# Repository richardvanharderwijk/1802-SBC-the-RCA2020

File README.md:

This project is the design of a small microcomputer system based on the RCA 1802 COSMAC CPU. 

The specifications of the system are:

• RCA 1802 CPU; 8 bit; up to 3,2 MHz clockspeed

• 64 kB RAM memory

• 8kBROM

• OS(ish): Utility to save, load, start programs; and examine registers and memory

• TTY serial terminal connection, software UART

• 8 bit parallel in/out

• I2C interface; and a clock/calender unit

• All signals available via connectors

• Single 5V via USB port

The design includes a PCB of 10 x 13 cm; and a build and test protocol per unit to facilitate error finding during build.

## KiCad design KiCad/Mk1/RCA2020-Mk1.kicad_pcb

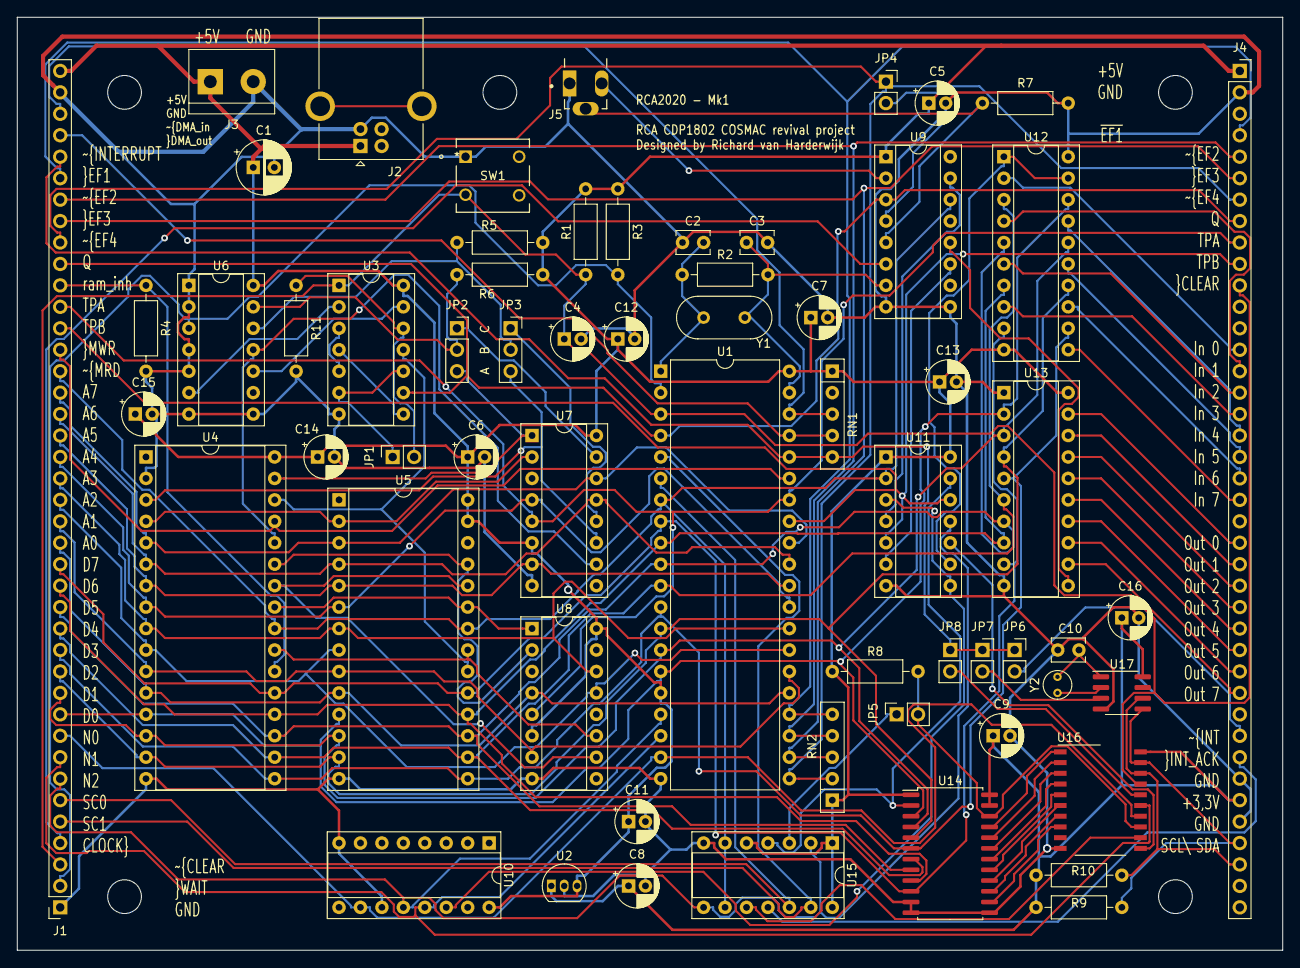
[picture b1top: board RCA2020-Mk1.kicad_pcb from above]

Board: 2 copper layers, 149.9 x 110.5 mm, 62 parts (0 on the bottom side), 106 nets.

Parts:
C1: 10uF; CP_Radial_D6.3mm_P2.50mm
C2, C3: 47pF; C_Disc_D3.8mm_W2.6mm_P2.50mm
C4: 1,5uF; CP_Radial_D5.0mm_P2.00mm
C5, C6, C7, C8, C9, C11, C12, C13, C14, C15, C16: 0,22uF; CP_Radial_D5.0mm_P2.00mm
C10: 20pF; C_Disc_D3.8mm_W2.6mm_P2.50mm
J1, J4: Conn_01x40_Female; PinSocket_1x40_P2.54mm_Vertical
J2: USB_B; USB_B_OST_USB-B1HSxx_Horizontal
J3: Screw_Terminal_01x02; TerminalBlock_bornier-2_P5.08mm
J5: AudioJack3; Lumberg-1501_04-MFG
JP1, JP4, JP5: Jumper_2_Bridged; PinSocket_1x02_P2.54mm_Vertical
JP2, JP3: Jumper_3_Bridged12; PinSocket_1x03_P2.54mm_Vertical
JP6, JP7, JP8: Jumper_2_Open; PinSocket_1x02_P2.54mm_Vertical
R1: 100k; R_Axial_DIN0207_L6.3mm_D2.5mm_P10.16mm_Horizontal
R2: 6,8M; R_Axial_DIN0207_L6.3mm_D2.5mm_P10.16mm_Horizontal
R3, R4, R5, R6, R7, R8, R11: 47k; R_Axial_DIN0207_L6.3mm_D2.5mm_P10.16mm_Horizontal
R9, R10: 4k7; R_Axial_DIN0207_L6.3mm_D2.5mm_P10.16mm_Horizontal
RN1, RN2: 4x47k; R_Array_SIP5
SW1: SW_Push; RAFI_KeySwitch
U1: CDP1802ACE; DIP-40_W15.24mm
U2: L78L33_TO92; TO-92_Inline
U3: 4001; DIP-14_W7.62mm_Socket
U4: 628128_DIP32_SSOP32; DIP-32_W15.24mm_Socket
U5: 28C64; DIP-28_W15.24mm_Socket
U6: 4025; DIP-14_W7.62mm_Socket
U7, U8: 4042; DIP-16_W7.62mm_Socket
U9: 4049; DIP-16_W7.62mm_Socket
U10: 4028; DIP-16_W7.62mm_Socket
U11: 4023; DIP-14_W7.62mm_Socket
U12: 74HCT244; DIP-20_W7.62mm_Socket
U13: 74LS573; DIP-20_W7.62mm_Socket
U14: 74LVC4245AD; SOP-24_7.5x15.4mm_P1.27mm
U15: 4011; DIP-14_W7.62mm_Socket
U16: PCA9564PW; SO-20_12.8x7.5mm_P1.27mm
U17: PCF8563T; SOIC-8_3.9x4.9mm_P1.27mm
Y1: Crystal; Crystal_HC49-U_Vertical
Y2: 32.768 kHz; Crystal_Round_D3.0mm_Vertical

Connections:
+3V3: C8.1, C9.1, C16.1, J4.35, R9.1, R10.1, U2.1, U14.23, U14.24, U16.20, U17.8
+5V: C1.1, C5.1, C6.1, C7.1, C11.1, C12.1, C13.1, C14.1, C15.1, J1.40, J2.1, J3.1, J4.1, R1.1, R3.1, R5.1, R6.1, R8.1, RN1.1, RN2.1, U1.16, U1.40, U2.3, U3.14, U4.32, U5.27, U5.28, U6.14, U7.6, U7.16, U8.6, U8.16, U9.1, U10.16, U11.1, U11.14, U12.10, U13.20, U14.1, U15.1, U15.5, U15.14
/N-lines IO/N-In0: J4.14, U12.2
/N-lines IO/N-In1: J4.15, U12.4
/N-lines IO/N-In2: J4.16, U12.6
/N-lines IO/N-In3: J4.17, U12.8
/N-lines IO/N-In4: J4.18, U12.17
/N-lines IO/N-In5: J4.19, U12.15
/N-lines IO/N-In6: J4.20, U12.13
/N-lines IO/N-In7: J4.21, U12.11
/N-lines IO/N-Out0: J4.23, U13.19
/N-lines IO/N-Out1: J4.24, U13.18
/N-lines IO/N-Out2: J4.25, U13.17
/N-lines IO/N-Out3: J4.26, U13.16
/N-lines IO/N-Out4: J4.27, U13.15
/N-lines IO/N-Out5: J4.28, U13.14
/N-lines IO/N-Out6: J4.29, U13.13
/N-lines IO/N-Out7: J4.30, U13.12
/N-lines to I2C/SCL: J4.38, R10.2, U16.18, U17.6
/N-lines to I2C/SDA: J4.37, R9.2, U16.19, U17.5
/N-lines to I2C/~INT: J4.32, JP6.2
/N-lines to I2C/~INT_ACK: J4.33, U15.11
/RAM+ROM/EXTERNAL_RAM_INHIBIT: J1.30, R4.1, U4.22
A0: J1.18, U1.25, U4.12, U5.10, U8.4
A1: J1.19, U1.26, U4.11, U5.9, U8.7
A2: J1.20, U1.27, U4.10, U5.8, U8.13
A3: J1.21, U1.28, U4.9, U5.7, U8.14
A4: J1.22, U1.29, U4.8, U5.6, U7.4
A5: J1.23, U1.30, U4.7, U5.5, U7.7
A6: J1.24, U1.31, U4.6, U5.4, U7.13
A7: J1.25, U1.32, U4.5, U5.3, U7.14
A8: U4.27, U5.25, U8.2
A9: U4.26, U5.24, U8.10
A10: U4.23, U5.21, U8.11
A11: U4.25, U5.23, U8.1
A12: U4.4, U5.2, U7.2
A13: U4.28, U6.11, U7.10
A14: JP3.3, U4.3, U7.11
A15: JP2.3, U4.31, U7.1
CLOCK: J1.4, U9.6
D0: J1.10, U1.15, U4.13, U5.11, U12.18, U13.2, U14.3
D1: J1.11, U1.14, U4.14, U5.12, U12.16, U13.3, U14.4
D2: J1.12, U1.13, U4.15, U5.13, U12.14, U13.4, U14.5
D3: J1.13, U1.12, U4.17, U5.15, U12.12, U13.5, U14.6
D4: J1.14, U1.11, U4.18, U5.16, U12.3, U13.6, U14.7
D5: J1.15, U1.10, U4.19, U5.17, U12.5, U13.7, U14.8
D6: J1.16, U1.9, U4.20, U5.18, U12.7, U13.8, U14.9
D7: J1.17, U1.8, U4.21, U5.19, U12.9, U13.9, U14.10
GND: C1.2, C2.2, C3.2, C4.2, C5.2, C6.2, C7.2, C8.2, C9.2, C10.2, C11.2, C12.2, C13.2, C14.2, C15.2, C16.2, J1.1, J1.39, J2.4, J3.2, J4.2, J4.34, J4.36, J5.S, R4.2, R7.2, R11.2, SW1.1, U1.20, U2.2, U3.7, U4.2, U4.16, U5.14, U6.1, U6.2, U6.4, U6.5, U6.7, U6.8, U7.8, U8.8, U9.8, U9.9, U10.8, U10.11, U11.7, U12.20, U13.1, U13.10, U14.11, U14.12, U14.13, U15.7, U16.10, U17.4
N0: J1.9, U1.19, U10.10, U16.14
N1: J1.8, U1.18, U10.13, U16.15
N2: J1.7, U1.17, U10.12, U11.11, U15.2, U15.8
unnamed: C2.1, R2.1, U1.1, Y1.1
unnamed: C3.1, R2.2, U1.39, U9.7, Y1.2
unnamed: C10.1, U17.1, Y2.2
unnamed: J5.R, U9.2
unnamed: J5.T, R7.1, U9.5
unnamed: JP1.1, U3.6, U3.10
unnamed: JP1.2, R11.1, U3.12
unnamed: JP2.1, U7.15
unnamed: JP2.2, R6.2, U6.13
unnamed: JP3.1, U7.12
unnamed: JP3.2, R5.2, U6.12
unnamed: JP4.2, U9.4
unnamed: JP5.1, U15.3
unnamed: JP5.2, R8.2, U14.22, U16.13
unnamed: JP7.2, U17.3
unnamed: JP8.2, U16.16
unnamed: U3.2, U6.6
unnamed: U3.3, U3.5
unnamed: U3.4, U3.8
unnamed: U3.11, U4.30, U5.20
unnamed: U3.13, U6.10
unnamed: U10.14, U11.3, U11.8
unnamed: U9.15, U11.4
unnamed: U9.11, U11.6
unnamed: U11.9, U12.1, U12.19
unnamed: U11.10, U16.11
unnamed: U11.13, U14.2, U15.4
unnamed: U9.12, U13.11
unnamed: U14.14, U16.8
unnamed: U14.15, U16.7
unnamed: U14.16, U16.6
unnamed: U14.17, U16.5
unnamed: U14.18, U16.4
unnamed: U14.19, U16.3
unnamed: U14.20, U16.2
unnamed: U14.21, U16.1
unnamed: U15.10, U16.12
unnamed: U17.2, Y2.1
Q: J1.31, J4.8, U1.4, U3.9, U9.3
SC0: J1.6, U1.6, U15.12
SC1: J1.5, U1.5, U15.13
TPA: J1.29, J4.9, U1.34, U7.5, U8.5
TPB: J1.28, J4.10, U1.33, U11.5, U11.12
~CLEAR: C4.1, J1.3, J4.11, R1.2, SW1.2, U1.3, U3.1, U16.17
~DMA_IN: J1.38, RN1.3, U1.38
~DMA_OUT: J1.37, RN1.4, U1.37
~EF1: J1.35, J4.4, RN2.5, U1.24
~EF2: J1.34, J4.5, RN2.4, U1.23
~EF3: J1.33, J4.6, RN2.3, U1.22
~EF4: J1.32, J4.7, JP4.1, RN2.2, U1.21
~INTERRUPT: J1.36, JP6.1, JP7.1, JP8.1, RN1.5, U1.36
~MRD: J1.26, U1.7, U4.24, U5.22, U9.14, U11.2, U15.6, U15.9
~MWR: J1.27, U1.35, U4.29
~WAIT: J1.2, R3.2, U1.2, U6.3

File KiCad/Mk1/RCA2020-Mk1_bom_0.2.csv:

Component;Description;Part;References;Value;Footprint;Quantity Per PCB;Power;Datasheet
1;Unpolarized capacitor;C;C10;20pF;C_Disc_D3.8mm_W2.6mm_P2.50mm;1;;~
2;Unpolarized capacitor;C;C2 C3;47pF;C_Disc_D3.8mm_W2.6mm_P2.50mm;2;;~
3;Polarized capacitor;CP;C1;10uF;CP_Radial_D6.3mm_P2.50mm;1;;~
4;Polarized capacitor;CP;C4;1,5uF;CP_Radial_D5.0mm_P2.00mm;1;;~
5;Polarized capacitor;CP;C5 C6 C7 C8 C9 C11 C12 C13 C14 C15 C16;0,22uF;CP_Radial_D5.0mm_P2.00mm;11;;~
6;Audio Jack, 3 Poles (Stereo / TRS);AudioJack3;J5;AudioJack3;Lumberg-1501_04-MFG;1;;~
7;Generic connector, single row, 01x40, script generated (kicad-library-utils/schlib/autogen/connector/);Conn_01x40_Female;J1 J4;Conn_01x40_Female;PinSocket_1x40_P2.54mm_Vertical;2;;~
8;Generic screw terminal, single row, 01x02, script generated (kicad-library-utils/schlib/autogen/connector/);Screw_Terminal_01x02;J3;Screw_Terminal_01x02;TerminalBlock_bornier-2_P5.08mm;1;;~
9;USB Type B connector;USB_B;J2;USB_B;USB_B_OST_USB-B1HSxx_Horizontal;1;; ~
10;Jumper, 2-pole, closed/bridged;Jumper_2_Bridged;JP1 JP4 JP5;Jumper_2_Bridged;PinSocket_1x02_P2.54mm_Vertical;3;;~
11;Jumper, 2-pole, open;Jumper_2_Open;JP6 JP7 JP8;Jumper_2_Open;PinSocket_1x02_P2.54mm_Vertical;3;;~
12;Jumper, 3-pole, pins 1+2 closed/bridged;Jumper_3_Bridged12;JP2 JP3;Jumper_3_Bridged12;PinSocket_1x03_P2.54mm_Vertical;2;;~
13;Resistor;R;R9 R10;4k7;R_Axial_DIN0207_L6.3mm_D2.5mm_P10.16mm_Horizontal;2;0,010638298;~
14;Resistor;R;R3 R4 R5 R6 R7 R8 R11;47k;R_Axial_DIN0207_L6.3mm_D2.5mm_P10.16mm_Horizontal;7;0,003723404;~
15;Resistor;R;R1;100k;R_Axial_DIN0207_L6.3mm_D2.5mm_P10.16mm_Horizontal;1;;~
16;Resistor;R;R2;6,8M;R_Axial_DIN0207_L6.3mm_D2.5mm_P10.16mm_Horizontal;1;;~
17;4 resistor network, star topology, bussed resistors, small symbol;R_Network04;RN1 RN2;4x47k;R_Array_SIP5;2;0,003723404;http://www.vishay.com/docs/31509/csc.pdf
18;Push button switch, generic, two pins;SW_Push;SW1;SW_Push;RAFI_KeySwitch;1;;~
19;Paged Parallel EEPROM 64Kb (8K x 8), DIP-28/SOIC-28;28C64;U5;28C64;DIP-28_W15.24mm_Socket;1;0,15;Atmel
20;Quad Nor 2 inputs;4001;U3;4001;DIP-14_W7.62mm_Socket;1;;http://www.intersil.com/content/dam/Intersil/documents/cd40/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
21;Quad Nand 2 inputs;4011;U15;4011;DIP-14_W7.62mm_Socket;1;;http://www.intersil.com/content/dam/Intersil/documents/cd40/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
22;Triple Nand 3 inputs;4023;U11;4023;DIP-14_W7.62mm_Socket;1;;http://www.intersil.com/content/dam/Intersil/documents/cd40/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
23;Triple Nor 3 inputs;4025;U6;4025;DIP-14_W7.62mm_Socket;1;;http://www.intersil.com/content/dam/Intersil/documents/cd40/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
24;Decoder 4 to 10 lines;4028;U10;4028;DIP-16_W7.62mm_Socket;1;0,0025;http://www.intersil.com/content/dam/Intersil/documents/cd40/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
25;;4042;U7 U8;4042;DIP-16_W7.62mm_Socket;2;;
26;Hex Buffer Inverter;4049;U9;4049;DIP-16_W7.62mm_Socket;1;;http://www.intersil.com/content/dam/intersil/documents/cd40/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
27;128K x 8 High-Speed CMOS Static RAM, 55/70ns, DIP-32/SSOP-32;628128_DIP32_SSOP32;U4;628128_DIP32_SSOP32;DIP-32_W15.24mm_Socket;1;0,175;http://www.futurlec.com/Datasheet/Memory/628128.pdf
28;8-bit Buffer/Line Driver 3-state;74HCT244;U12;74HCT244;DIP-20_W7.62mm_Socket;1;0,0025;https://assets.nexperia.com/documents/data-sheet/74HC_HCT244.pdf
29;8-bit Latch 3-state outputs;74LS573;U13;74LS573;DIP-20_W7.62mm_Socket;1;;74xx/74hc573.pdf
30;;74LVC4245AD;U14;74LVC4245AD;SOP-24_7.5x15.4mm_P1.27mm;1;0,032;
31;8-bit, General Purpose, 5V, 3.2 MHz, DIP-40;CDP1802ACE;U1;CDP1802ACE;DIP-40_W15.24mm;1;0,004;http://www.cosmacelf.com/publications/data-sheets/cdp1802.pdf
32;Positive 100mA 30V Linear Regulator, Fixed Output 3.3V, TO-92;L78L33_TO92;U2;L78L33_TO92;TO-92_Inline;1;;http://www.st.com/content/ccc/resource/technical/document/da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
33;;PCA9564PW;U16;PCA9564PW;SO-20_12.8x7.5mm_P1.27mm;1;0,0198;
34;Realtime Clock/Calendar I2C Interface, SOIC-8;PCF8563T;U17;PCF8563T;SOIC-8_3.9x4.9mm_P1.27mm;1;0,0033;https://assets.nexperia.com/documents/data-sheet/PCF8563.pdf
35;Two pin crystal;Crystal;Y2;32.768 kHz;Crystal_Round_D3.0mm_Vertical;1;;~
36;Two pin crystal;Crystal;Y1;Crystal;Crystal_HC49-U_Vertical;1;;~
;;;;;;;0,407185106;
;;;;;;;;
;;;;;;;;
;;;;;;;;
;;;;;;;;
Component Groups:;36;;;;;;;
Component Count:;62;;;;;;;
Fitted Components:;62;;;;;;;
Number of PCBs:;1;;;;;;;
Total components:;62;;;;;;;
Schematic Version:;0.2;;;;;;;
Schematic Date:;20-02-2021;;;;;;;
PCB Variant:;udefault;;;;;;;
BoM Date:;2021 February 22, Monday 21:50:06;;;;;;;
Schematic Source:;RCA2020-Mk1.sch;;;;;;;
KiCad Version:;Eeschema (5.1.5-0-10_14);;;;;;;

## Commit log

2024-02-17 Update README.md
    Initial version, abstract from Design, Build and Test Manual
2024-02-17 Create ...
2024-02-18 Add files via upload
    The main documentation
2024-02-18 Main documentation: Design, Build, Test
2024-02-18 Create tmp
2024-02-18 OS, based on RCA's UT4 utility
    Details in design, build, test doc
2024-02-18 KiCad files RCA2020-Mk1
2024-02-18 RCA2020 Gerbers Mk1
2024-02-18 RCA2020 KiCad files Mk1
2024-02-18 Description of KNOWN-ERRORS
2024-02-18 2 known errors in Mk1
2024-02-18 Known Errors
2025-09-02 Bump actions/checkout from 4 to 5
    Bumps [actions/checkout](https://github.com/actions/checkout) from 4 to 5.
    - [Release notes](https://github.com/actions/checkout/releases)
    - [Changelog](https://github.com/actions/checkout/blob/main/CHANGELOG.md)
    - [Commits](https://github.com/actions/checkout/compare/v4...v5)
    ---
    updated-dependencies:
2025-12-01 Bump actions/checkout from 4 to 6
    Bumps [actions/checkout](https://github.com/actions/checkout) from 4 to 6.
    - [Release notes](https://github.com/actions/checkout/releases)
    - [Changelog](https://github.com/actions/checkout/blob/main/CHANGELOG.md)
    - [Commits](https://github.com/actions/checkout/compare/v4...v6)
    ---
    updated-dependencies:

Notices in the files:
parts and their libraries:
Copyright 2016 Accelerated Designs. All rights reserved.
